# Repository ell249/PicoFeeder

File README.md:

# PicoFeeder
RP2040 Pico W with integrated Stepper Driver Board

See https://ell-tech.com/dog-feeder/ running ESPHome 2023.6.4 for more information

Adapted from the Big Easy Driver by Brian Schmalz https://www.schmalzhaus.com/BigEasyDriver/ and adapted by Sparkfun https://github.com/sparkfun/Big_Easy_Driver/tree/V_HW1.6a_FW1.0 

Licenced under https://creativecommons.org/licenses/by-sa/3.0/

Please note the following changes in this Big Easy Driver V1.6E from the original V1.6:
- Buck converter has been incorporated to replace LM317 linear regulator to provide additional power for the RP2040.
- Enable pin now pulled-up by default (instead of down) to start stepper driver disabled. Cut and solder JP15 to enable by default.

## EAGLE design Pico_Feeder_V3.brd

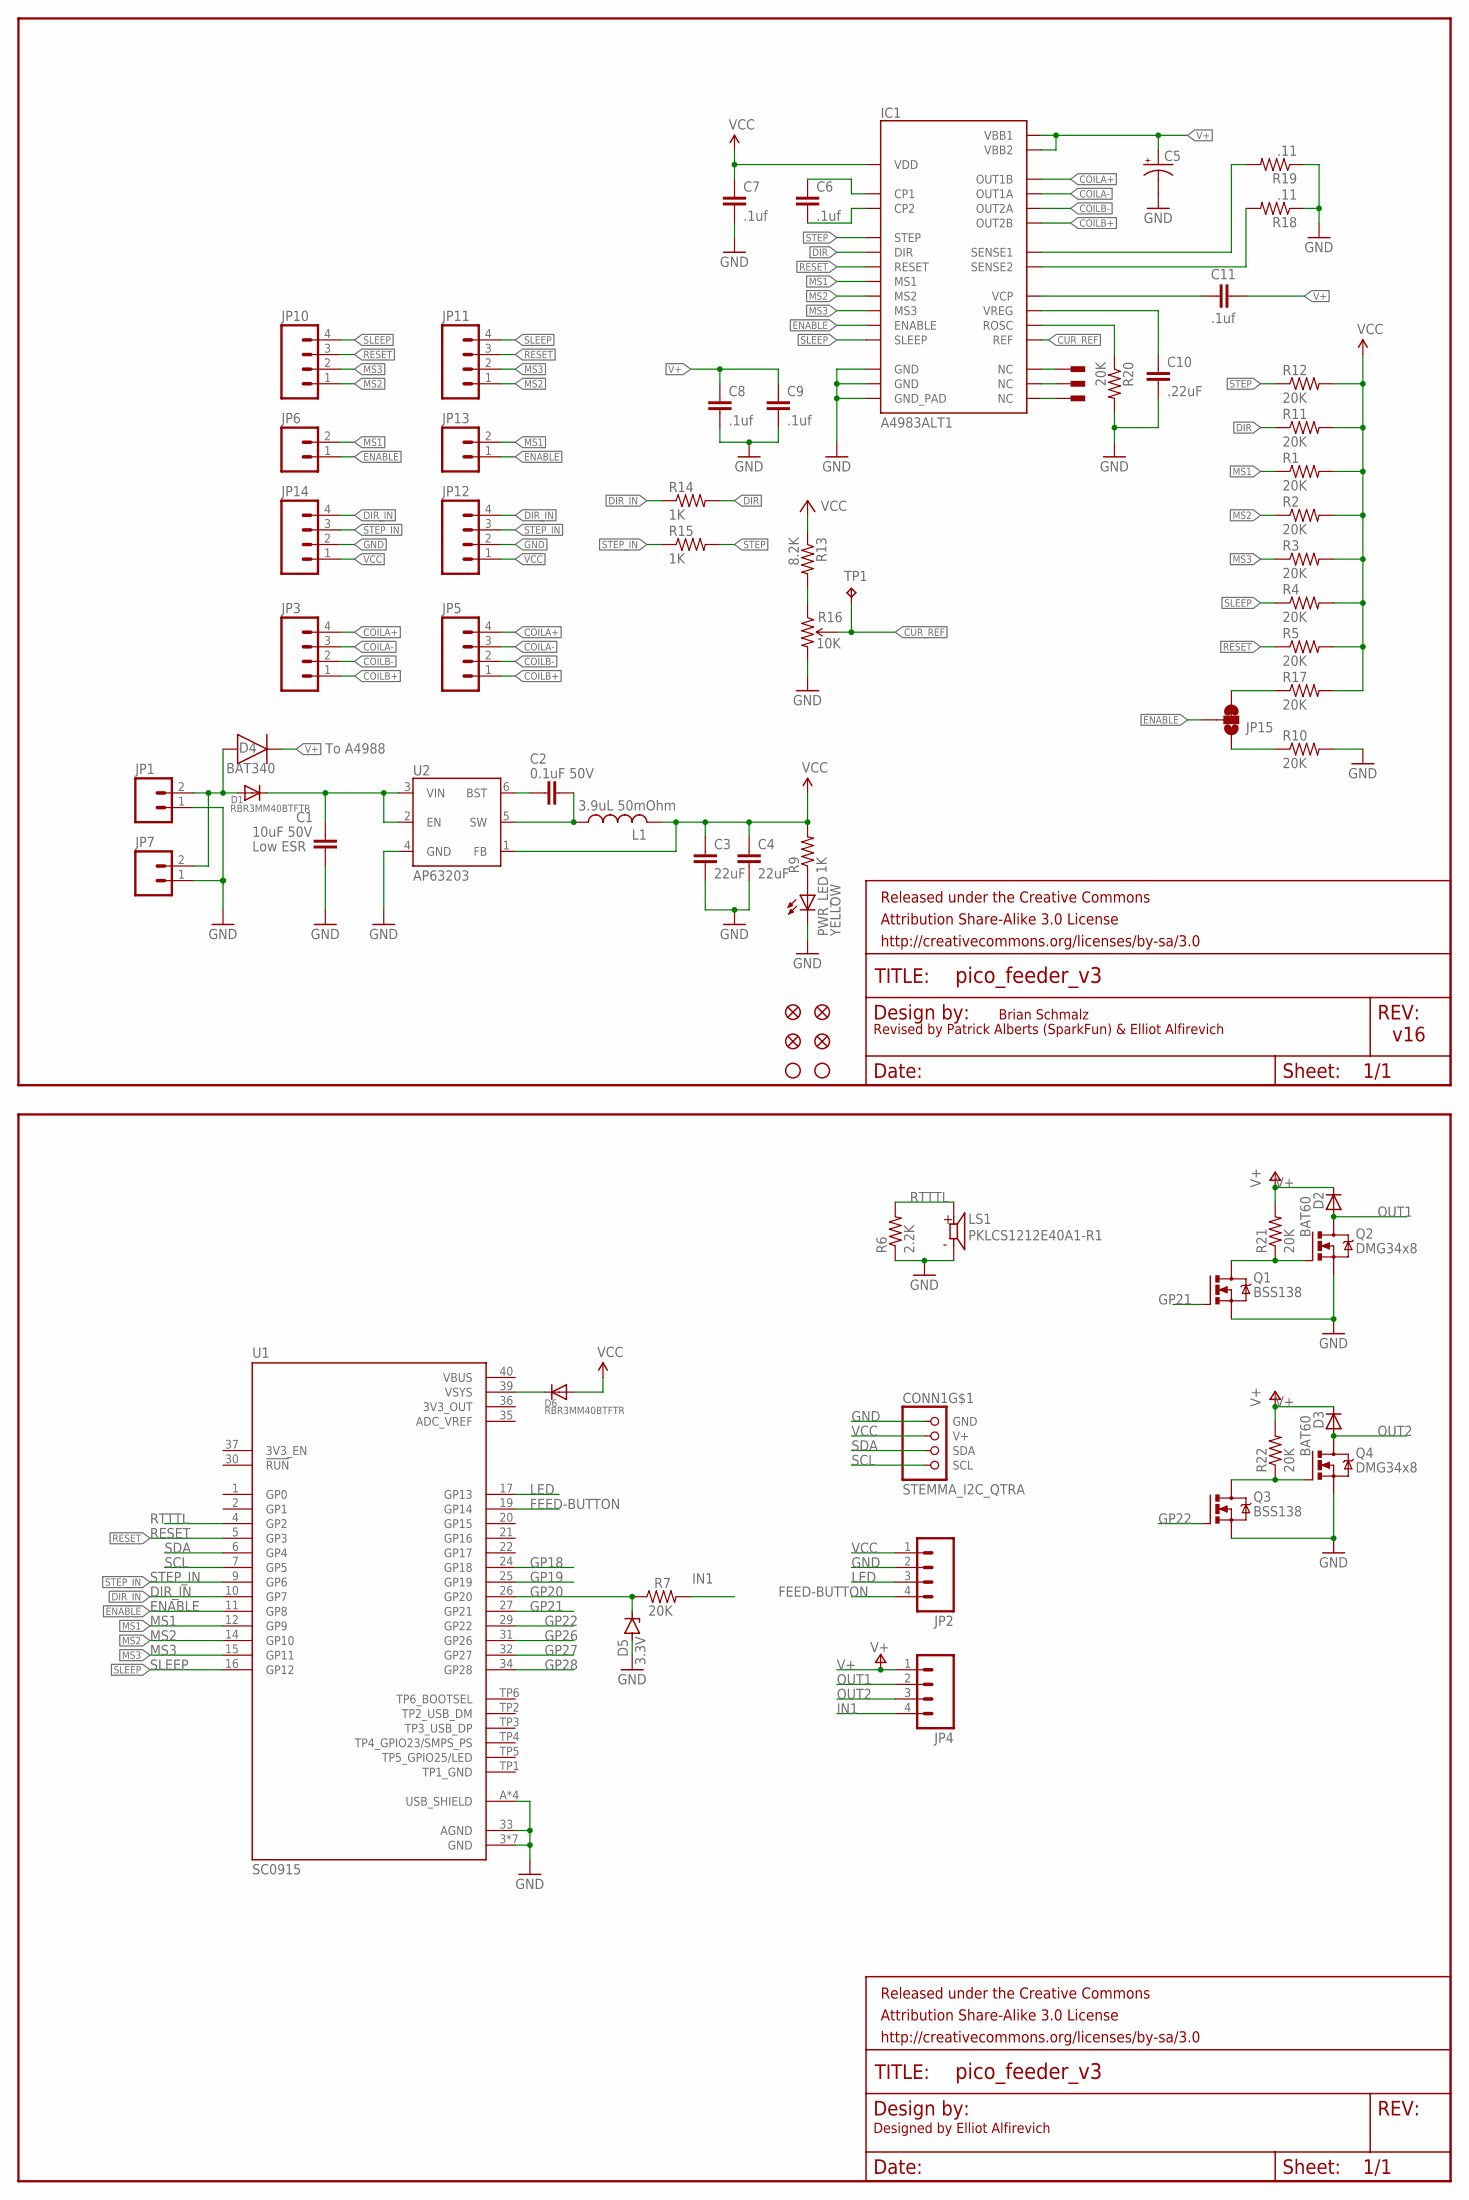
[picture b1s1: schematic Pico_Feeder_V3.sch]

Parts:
C1: 10uF 50V; CAPC2012X110
C2: 0.1uF 50V; CAPC2012X110
C3, C4: 22uF; 0603-CAP
C5: CPOL-USD; PANASONIC_D
C6, C7, C8, C9, C11: .1uf; 0603-CAP
C10: .22uF; 0603-CAP
CONN1: STEMMA_I2C_QTRA; JST_SH4_RA
D1, D6: RBR3MM40BTFTR; SOD-123FL
D2, D3: BAT60; SOD323-R
D4: BAT340; DIOM5226X290N
D5: 3.3V; SODFL2513X70
FID1, FID2, FID3, FID4: FIDUCIAL1X2; FIDUCIAL-1X2
FRAME1, FRAME2: FRAME-LETTER; CREATIVE_COMMONS
IC1: A4983ALT1; QFN-28-5MM_ALT1
JP1, JP6: M02PTH; 1X02
JP2, JP4, JP5, JP11, JP12: M04SCREW_LOCK; SCREWTERMINAL-3.5MM-4_LOCK
JP3, JP10, JP14: M04PTH; 1X04
JP7, JP13: M023.5MM_LOCK; SCREWTERMINAL-3.5MM-2_LOCK
JP8, JP9: STAND-OFF
JP15: JUMPER-SMT_3_1-NC_TRACE_SILK; SMT-JUMPER_3_1-NC_TRACE_SILK
L1: 3.9uL 50mOhm; LQH55; LCSC C5289415
LS1: PKLCS1212E40A1-R1; SPKR_PKLCS1212E40A1-R1
PWR_LED: YELLOW; LED-0603
Q1, Q3: BSS138; SOT23
Q2, Q4: DMG34x8; SOT23
R1, R2, R3, R4, R5, R7, R10, R11, R12, R17, R20, R21, R22: 20K; 0603-RES
R6: 2.2K; 0603-RES
R9, R14, R15: 1K; 0603-RES
R13: 8.2K; 0603-RES
R16: 10K; TRIMPOT-3MM-2
R18, R19: .11; R2010
TP1: TPPAD1-13; P1-13
U1: SC0915; MODULE_SC0915
U2: AP63203; SOT23-6
U$3, U$4, U$5: PAD; PAD-0.008

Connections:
3V3_OUT: U1.36 (3V3_OUT)
ADC_VREF: U1.35 (ADC_VREF)
COILA+: IC1.P$21 (OUT1B), JP3.4, JP5.4
COILA-: IC1.P$24 (OUT1A), JP3.3, JP5.3
COILB+: IC1.P$1 (OUT2B), JP3.1, JP5.1
COILB-: IC1.P$26 (OUT2A), JP3.2, JP5.2
CUR_REF: IC1.P$17 (REF), R16.2 (WIPER), TP1.TP
DIR: IC1.P$19 (DIR), R11.1, R14.2
DIR_IN: JP12.4, JP14.4, R14.1, U1.10 (GP7)
ENABLE: IC1.P$2 (ENABLE), JP6.1, JP13.1, JP15.2, U1.11 (GP8)
FEED-BUTTON: JP2.4, U1.19 (GP14)
GND: C1.2, C3.2, C4.2, C5.-, C7.2, C8.2, C9.2, C10.2, CONN1.1 (GND), D5.2 (A), IC1.P$3 (GND), IC1.P$18 (GND), IC1.P$29 (GND_PAD), JP1.1, JP2.2, JP7.1, JP12.2, JP14.2, LS1.N, PWR_LED.C, Q1.2 (S), Q2.2 (S), Q3.2 (S), Q4.2 (S), R6.1, R10.2, R16.3 (CW), R18.1, R19.1, R20.2, U1.3 (GND), U1.8 (GND), U1.13 (GND), U1.18 (GND), U1.23 (GND), U1.28 (GND), U1.33 (AGND), U1.38 (GND), U1.A (USB_SHIELD), U1.B (USB_SHIELD), U1.C (USB_SHIELD), U1.D (USB_SHIELD), U2.4 (GND)
GP18: U1.24 (GP18)
GP19: U1.25 (GP19)
GP20: D5.1 (C), R7.1, U1.26 (GP20)
GP21: Q1.1 (G), U1.27 (GP21)
GP22: Q3.1 (G), U1.29 (GP22)
GP26: U1.31 (GP26)
GP27: U1.32 (GP27)
GP28: U1.34 (GP28)
IN1: JP4.4, R7.2
LED: JP2.3, U1.17 (GP13)
MS1: IC1.P$9 (MS1), JP6.2, JP13.2, R1.1, U1.12 (GP9)
MS2: IC1.P$10 (MS2), JP10.1, JP11.1, R2.1, U1.14 (GP10)
MS3: IC1.P$11 (MS3), JP10.2, JP11.2, R3.1, U1.15 (GP11)
unnamed: C2.1, U2.6 (BST)
unnamed: PWR_LED.A, R9.1
unnamed: R13.2, R16.1 (CCW)
unnamed: C2.2, L1.1, U2.5 (SW)
unnamed: IC1.P$7 (NC), U$3.P$1
unnamed: C1.1, D1.C, U2.2 (EN), U2.3 (VIN)
unnamed: IC1.P$20 (NC), U$4.P$1
unnamed: C6.1, IC1.P$4 (CP1)
unnamed: C6.2, IC1.P$5 (CP2)
unnamed: IC1.P$25 (NC), U$5.P$1
unnamed: Q1.3 (D), Q2.1 (G), R21.1
unnamed: D1.A, D4.2 (A), JP1.2, JP7.2
unnamed: D6.C, U1.39 (VSYS)
unnamed: Q3.3 (D), Q4.1 (G), R22.1
unnamed: JP15.3, R17.1
unnamed: JP15.1, R10.1
unnamed: IC1.P$13 (ROSC), R20.1
unnamed: C10.1, IC1.P$8 (VREG)
unnamed: C11.1, IC1.P$6 (VCP)
unnamed: IC1.P$27 (SENSE2), R18.2
unnamed: IC1.P$23 (SENSE1), R19.2
OUT1: D2.A, JP4.2, Q2.3 (D)
OUT2: D3.A, JP4.3, Q4.3 (D)
RESET: IC1.P$12 (RESET), JP10.3, JP11.3, R5.1, U1.5 (GP3)
RTTTL: LS1.P, R6.2, U1.4 (GP2)
SCL: CONN1.4 (SCL), U1.7 (GP5)
SDA: CONN1.3 (SDA), U1.6 (GP4)
SLEEP: IC1.P$14 (SLEEP), JP10.4, JP11.4, R4.1, U1.16 (GP12)
STEP: IC1.P$16 (STEP), R12.1, R15.2
STEP_IN: JP12.3, JP14.3, R15.1, U1.9 (GP6)
TP1_GND: U1.TP1 (TP1_GND)
V+: C5.+, C8.1, C9.1, C11.2, D2.C, D3.C, D4.1 (C), IC1.P$22 (VBB1), IC1.P$28 (VBB2), JP4.1, R21.2, R22.2
VBUS: U1.40 (VBUS)
VCC: C3.1, C4.1, C7.1, CONN1.2 (V+), D6.A, IC1.P$15 (VDD), JP2.1, JP12.1, JP14.1, L1.2, R1.2, R2.2, R3.2, R4.2, R5.2, R9.2, R11.2, R12.2, R13.1, R17.2, U2.1 (FB)

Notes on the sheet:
Brian Schmalz
v16
Revised by Patrick Alberts (SparkFun) & Elliot Alfirevich
Designed by Elliot Alfirevich
Low ESR
To A4988

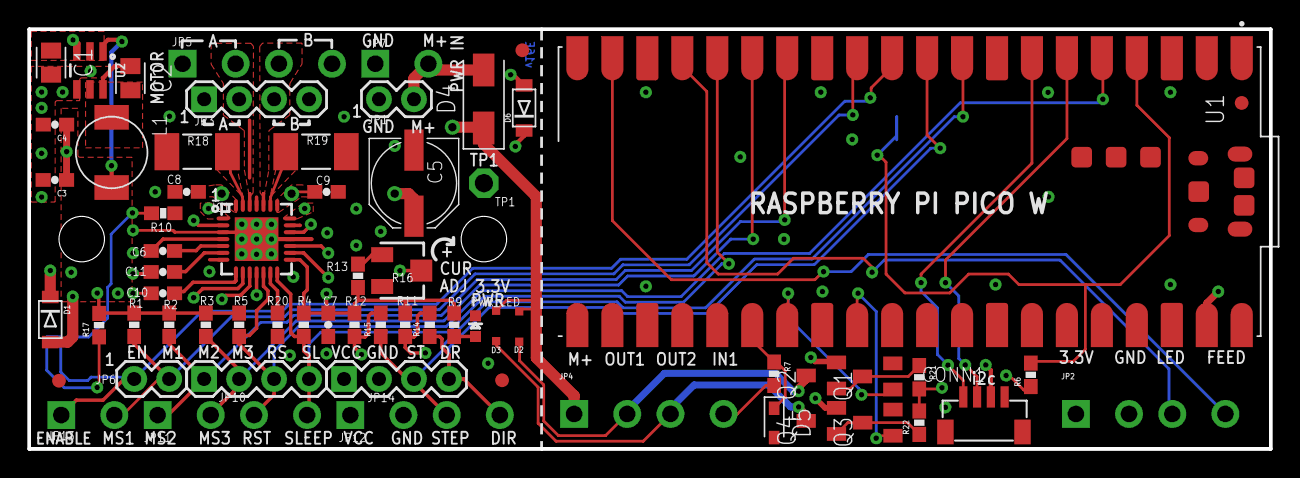
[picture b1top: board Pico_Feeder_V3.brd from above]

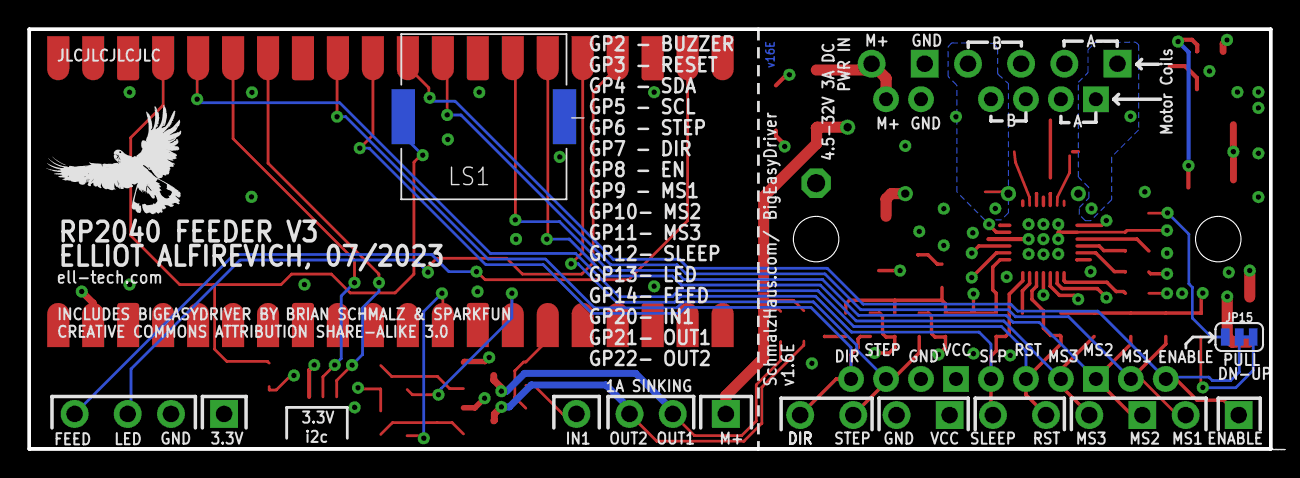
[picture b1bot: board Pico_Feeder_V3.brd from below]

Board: 4 copper layers, 90.2 x 30.5 mm, 74 parts (2 on the bottom side), 50 nets.

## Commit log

2023-07-05 Initial fab
2023-07-05 First README.md
2023-07-05 Initial ESPHome software config
2023-07-05 Create LICENSE

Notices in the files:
Pico_Feeder_V3.brd:
CREATIVE COMMONS ATTRIBUTION SHARE-ALIKE 3.0
Pico_Feeder_V3.sch:
Changed license from CC by 3.0 to CC by-sa 3.0
parts and their libraries:
SparkFun-Aesthetics: Licensing: CC v3.0 Share-Alike You are welcome to use this library for commercial purposes.
SparkFun-Aesthetics: Released under the Creative Commons Attribution Share-Alike 3.0 License
SparkFun-Aesthetics: http://creativecommons.org/licenses/by-sa/3.0
